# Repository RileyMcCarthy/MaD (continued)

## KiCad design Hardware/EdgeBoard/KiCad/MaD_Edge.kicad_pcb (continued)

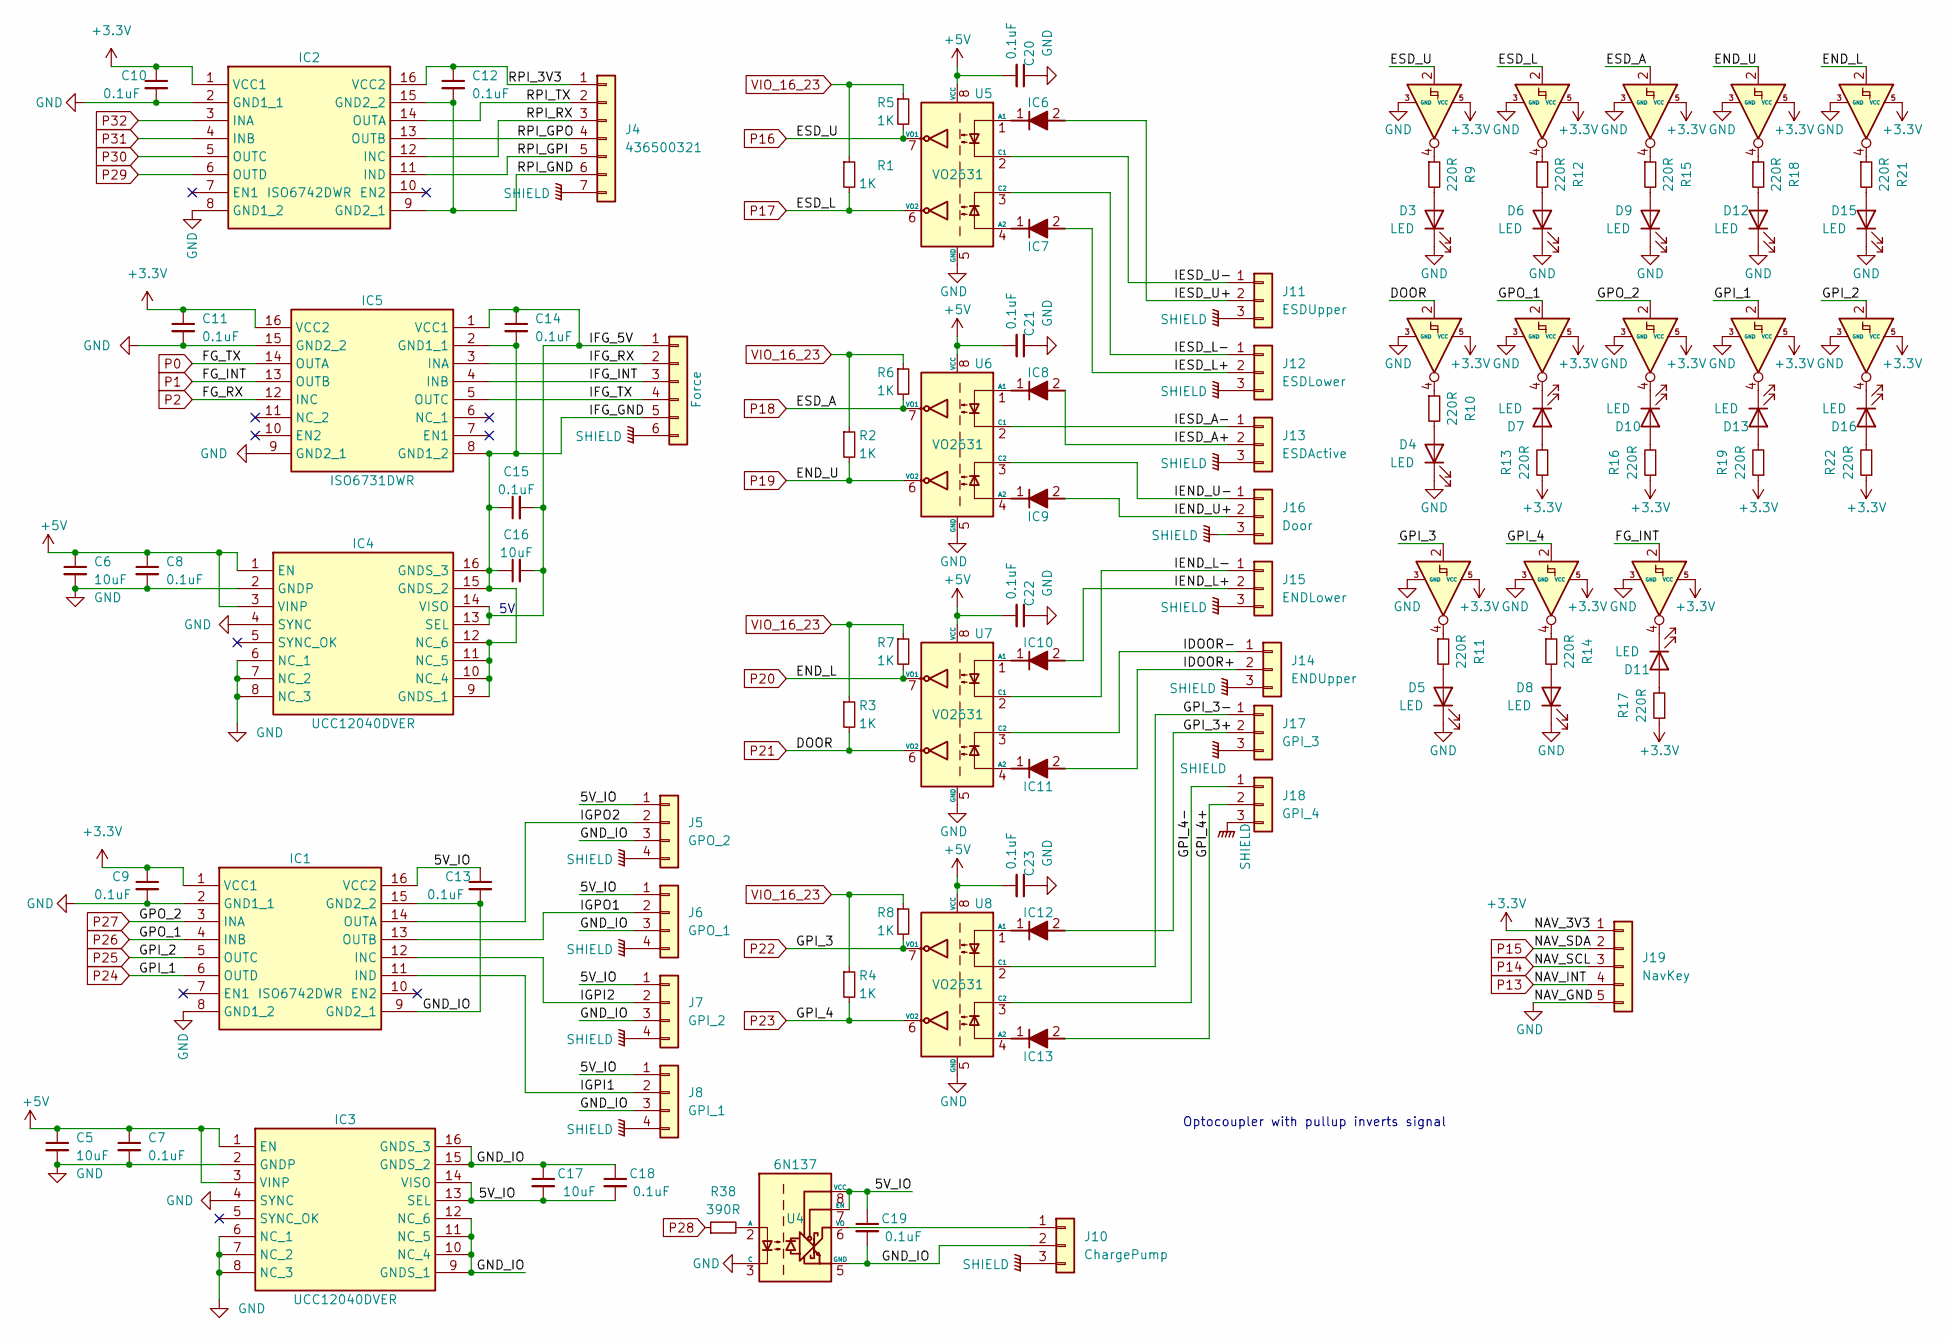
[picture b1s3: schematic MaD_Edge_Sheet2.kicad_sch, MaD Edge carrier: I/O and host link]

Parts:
C5, C6, C16, C17: 10uF; C_1206_3216Metric; Manufacturer_Part_Number CL31A106MAHNNNE; DIGIKEY 1276-1181-1-ND
C7, C8, C9, C10, C11, C12, C13, C14, C15, C18, C19, C20, C21, C22, C23: 0.1uF; C_0603_1608Metric; Manufacturer_Part_Number CL05A104KA5NNNC; DIGIKEY 1276-1043-1-ND
D3, D4, D5, D6, D7, D8, D9, D10, D11, D12, D13, D15, D16: LED; LED_0603_1608Metric; Manufacturer_Part_Number LTST-C190KGKT; DIGIKEY 160-1435-1-ND
IC1, IC2: ISO6742DWR; SOIC127P1030X265-16N; Manufacturer_Part_Number ISO6742DWR; DIGIKEY 296-ISO6742DWRCT-ND
IC3, IC4: UCC12040DVER; SOIC127P1030X265-16N; Manufacturer_Part_Number UCC12040DVER; DIGIKEY 296-UCC12040DVERCT-ND
IC5: ISO6731DWR; SOIC127P1030X265-16N; Manufacturer_Part_Number ISO6731DWR; DIGIKEY 296-ISO6731DWRCT-ND
IC6, IC7, IC8, IC9, IC10, IC11, IC12, IC13: NSI50010YT1G; SOD3716X135N; Manufacturer_Part_Number NSI50010YT1G; DIGIKEY NSI50010YT1G
J4: 436500321; Molex_Micro-Fit_3.0_43045-0618_2x03-1MP_P3.00mm_Vertical; Manufacturer_Part_Number 0430450618; DIGIKEY WM1803CT-ND
J5: GPO_2; Molex_Micro-Fit_3.0_43045-0415_2x02_P3.00mm_Vertical; Manufacturer_Part_Number 0430450415; DIGIKEY WM3251CT-ND
J6: GPO_1; Molex_Micro-Fit_3.0_43045-0415_2x02_P3.00mm_Vertical; Manufacturer_Part_Number 0430450415; DIGIKEY WM3251CT-ND
J7: GPI_2; Molex_Micro-Fit_3.0_43045-0415_2x02_P3.00mm_Vertical; Manufacturer_Part_Number 0430450415; DIGIKEY WM3251CT-ND
J8: GPI_1; Molex_Micro-Fit_3.0_43045-0415_2x02_P3.00mm_Vertical; Manufacturer_Part_Number 0430450415; DIGIKEY WM3251CT-ND
J9: Force; Molex_Micro-Fit_3.0_43045-0615_2x03_P3.00mm_Vertical; Manufacturer_Part_Number 0430450615; DIGIKEY WM6688CT-ND
J10: ChargePump; Molex_Micro-Fit_3.0_43650-0321_1x03_P3.00mm_Vertical; Manufacturer_Part_Number 0436500321; DIGIKEY WM14311CT-ND
J11: ESDUpper; Molex_Micro-Fit_3.0_43650-0321_1x03_P3.00mm_Vertical; Manufacturer_Part_Number 0436500321; DIGIKEY WM14311CT-ND
J12: ESDLower; Molex_Micro-Fit_3.0_43650-0321_1x03_P3.00mm_Vertical; Manufacturer_Part_Number 0436500321; DIGIKEY WM14311CT-ND
J13: ESDActive; Molex_Micro-Fit_3.0_43650-0321_1x03_P3.00mm_Vertical; Manufacturer_Part_Number 0436500321; DIGIKEY WM14311CT-ND
J14: ENDUpper; Molex_Micro-Fit_3.0_43650-0321_1x03_P3.00mm_Vertical; Manufacturer_Part_Number 0436500321; DIGIKEY WM14311CT-ND
J15: ENDLower; Molex_Micro-Fit_3.0_43650-0321_1x03_P3.00mm_Vertical; Manufacturer_Part_Number 0436500321; DIGIKEY WM14311CT-ND
J16: Door; Molex_Micro-Fit_3.0_43650-0321_1x03_P3.00mm_Vertical; Manufacturer_Part_Number 0436500321; DIGIKEY WM14311CT-ND
J17: GPI_3; Molex_Micro-Fit_3.0_43650-0321_1x03_P3.00mm_Vertical; Manufacturer_Part_Number 0436500321; DIGIKEY WM14311CT-ND
J18: GPI_4; Molex_Micro-Fit_3.0_43650-0321_1x03_P3.00mm_Vertical; Manufacturer_Part_Number 0436500321; DIGIKEY WM14311CT-ND
J19: NavKey; Molex_Micro-Fit_3.0_43650-0521_1x05_P3.00mm_Vertical; Manufacturer_Part_Number 0436500521; DIGIKEY WM14316CT-ND
R1, R2, R3, R4, R5, R6, R7, R8: 1K; R_0603_1608Metric; manufacturer_part_numbe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 0603WAF1001T5E; LCSC C21190
R9, R10, R11, R12, R13, R14, R15, R16, R17, R18, R19, R21, R22: 220R; R_0603_1608Metric; manufacturer_part_numbe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 0603WAF2200T5E; LCSC C22962
R38: 390R; R_0603_1608Metric; manufacturer_part_numbe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 0603WAF3900T5E; LCSC C23151
U4: 6N137; DIP-8_W7.62mm; Manufacturer_Part_Number 6N137; LCSC C2904408
U5, U6, U7, U8: VO2631; DIP-8_W7.62mm; Manufacturer_Part_Number VO2631; LCSC C511606
U9, U10, U11, U12, U13, U14, U15, U16, U17, U18, U19, U21, U22: SN74LVC1G14DBV; SOT-23-5; Manufacturer_Part_Number SN74LVC1G14DBVT; LCSC C5250998

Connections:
+3.3V: C9.1, C10.1, C11.1, IC1.1 (VCC1), IC2.1 (VCC1), IC5.16 (VCC2), J19.1, R13.1, R16.1, R17.1, R19.1, R22.1, U9.5 (VCC), U10.5 (VCC), U11.5 (VCC), U12.5 (VCC), U13.5 (VCC), U14.5 (VCC), U15.5 (VCC), U16.5 (VCC), U17.5 (VCC), U18.5 (VCC), U19.5 (VCC), U21.5 (VCC), U22.5 (VCC); also elsewhere on the board
+5V: C5.1, C6.1, C7.1, C8.1, C20.2, C21.2, C22.2, C23.2, IC3.1 (EN), IC3.3 (VINP), IC4.1 (EN), IC4.3 (VINP), U5.8 (VCC), U6.8 (VCC), U7.8 (VCC), U8.8 (VCC); also elsewhere on the board
/MaD_Edge_Sheet2/5V_IO: C13.1, C17.2, C18.2, C19.1, IC1.16 (VCC2), IC3.13 (SEL), IC3.14 (VISO), J5.1, J6.1, J7.1, J8.1, U4.7 (EN), U4.8 (VCC)
/MaD_Edge_Sheet2/GND_IO: C13.2, C17.1, C18.1, C19.2, IC1.9 (GND2_1), IC1.15 (GND2_2), IC3.9 (GNDS_1), IC3.10 (NC_4), IC3.11 (NC_5), IC3.12 (NC_6), IC3.15 (GNDS_2), IC3.16 (GNDS_3), J5.3, J6.3, J7.3, J8.3, J10.2, U4.5 (GND)
/MaD_Edge_Sheet2/GPI_3+: IC12.2 (A), J17.2
/MaD_Edge_Sheet2/GPI_3-: J17.1, U8.2 (C1)
/MaD_Edge_Sheet2/GPI_4+: IC13.2 (A), J18.2
/MaD_Edge_Sheet2/GPI_4-: J18.1, U8.3 (C2)
/MaD_Edge_Sheet2/IDOOR+: IC11.2 (A), J14.2
/MaD_Edge_Sheet2/IDOOR-: J14.1, U7.3 (C2)
/MaD_Edge_Sheet2/IEND_L+: IC10.2 (A), J15.2
/MaD_Edge_Sheet2/IEND_L-: J15.1, U7.2 (C1)
/MaD_Edge_Sheet2/IEND_U+: IC9.2 (A), J16.2
/MaD_Edge_Sheet2/IEND_U-: J16.1, U6.3 (C2)
/MaD_Edge_Sheet2/IESD_A+: IC8.2 (A), J13.2
/MaD_Edge_Sheet2/IESD_A-: J13.1, U6.2 (C1)
/MaD_Edge_Sheet2/IESD_L+: IC7.2 (A), J12.2
/MaD_Edge_Sheet2/IESD_L-: J12.1, U5.3 (C2)
/MaD_Edge_Sheet2/IESD_U+: IC6.2 (A), J11.2
/MaD_Edge_Sheet2/IESD_U-: J11.1, U5.2 (C1)
/MaD_Edge_Sheet2/IFG_5V: C14.1, C15.2, C16.2, IC4.13 (SEL), IC4.14 (VISO), IC5.1 (VCC1), J9.1
/MaD_Edge_Sheet2/IFG_GND: C14.2, C15.1, C16.1, IC4.9 (GNDS_1), IC4.10 (NC_4), IC4.11 (NC_5), IC4.12 (NC_6), IC4.15 (GNDS_2), IC4.16 (GNDS_3), IC5.2 (GND1_1), IC5.8 (GND1_2), J9.5
/MaD_Edge_Sheet2/IFG_INT: IC5.4 (INB), J9.3
/MaD_Edge_Sheet2/IFG_RX: IC5.3 (INA), J9.2
/MaD_Edge_Sheet2/IFG_TX: IC5.5 (OUTC), J9.4
/MaD_Edge_Sheet2/IGPI1: IC1.11 (IND), J8.2
/MaD_Edge_Sheet2/IGPI2: IC1.12 (INC), J7.2
/MaD_Edge_Sheet2/IGPO1: IC1.13 (OUTB), J6.2
/MaD_Edge_Sheet2/IGPO2: IC1.14 (OUTA), J5.2
/MaD_Edge_Sheet2/RPI_3V3: C12.1, IC2.16 (VCC2), J4.1
/MaD_Edge_Sheet2/RPI_GND: C12.2, IC2.9 (GND2_1), IC2.15 (GND2_2), J4.6
/MaD_Edge_Sheet2/RPI_GPI: IC2.11 (IND), J4.5
/MaD_Edge_Sheet2/RPI_GPO: IC2.13 (OUTB), J4.4
/MaD_Edge_Sheet2/RPI_RX: IC2.12 (INC), J4.3
/MaD_Edge_Sheet2/RPI_TX: IC2.14 (OUTA), J4.2
GND: C5.2, C6.2, C7.2, C8.2, C9.2, C10.2, C11.2, C20.1, C21.1, C22.1, C23.1, D3.1 (K), D4.1 (K), D5.1 (K), D6.1 (K), D8.1 (K), D9.1 (K), D12.1 (K), D15.1 (K), IC1.2 (GND1_1), IC1.8 (GND1_2), IC2.2 (GND1_1), IC2.8 (GND1_2), IC3.2 (GNDP), IC3.4 (SYNC), IC3.6 (NC_1), IC3.7 (NC_2), IC3.8 (NC_3), IC4.2 (GNDP), IC4.4 (SYNC), IC4.6 (NC_1), IC4.7 (NC_2), IC4.8 (NC_3), IC5.9 (GND2_1), IC5.15 (GND2_2), J19.5, U4.3 (C), U5.5 (GND), U6.5 (GND), U7.5 (GND), U8.5 (GND), U9.3 (GND), U10.3 (GND), U11.3 (GND), U12.3 (GND), U13.3 (GND), U14.3 (GND), U15.3 (GND), U16.3 (GND), U17.3 (GND), U18.3 (GND), U19.3 (GND), U21.3 (GND), U22.3 (GND); also elsewhere on the board
unnamed: D3.2 (A), R9.2
unnamed: D4.2 (A), R10.2
unnamed: D5.2 (A), R11.2
unnamed: D6.2 (A), R12.2
unnamed: D7.2 (A), R13.2
unnamed: D7.1 (K), U13.4
unnamed: D8.2 (A), R14.2
unnamed: D9.2 (A), R15.2
unnamed: D10.2 (A), R16.2
unnamed: D10.1 (K), U16.4
unnamed: D11.2 (A), R17.2
unnamed: D11.1 (K), U17.4
unnamed: D12.2 (A), R18.2
unnamed: D13.2 (A), R19.2
unnamed: D13.1 (K), U19.4
unnamed: D15.2 (A), R21.2
unnamed: D16.2 (A), R22.2
unnamed: D16.1 (K), U22.4
unnamed: IC6.1 (K), U5.1 (A1)
unnamed: IC7.1 (K), U5.4 (A2)
unnamed: IC8.1 (K), U6.1 (A1)
unnamed: IC9.1 (K), U6.4 (A2)
unnamed: IC10.1 (K), U7.1 (A1)
unnamed: IC11.1 (K), U7.4 (A2)
unnamed: IC12.1 (K), U8.1 (A1)
unnamed: IC13.1 (K), U8.4 (A2)
unnamed: J10.1, U4.6 (VO)
unnamed: R9.1, U9.4
unnamed: R10.1, U10.4
unnamed: R11.1, U11.4
unnamed: R12.1, U12.4
unnamed: R14.1, U14.4
unnamed: R15.1, U15.4
unnamed: R18.1, U18.4
unnamed: R21.1, U21.4
unnamed: R38.2, U4.2 (A)
P0: IC5.14 (OUTA); also elsewhere on the board
P1: IC5.13 (OUTB), U17.2; also elsewhere on the board
P2: IC5.12 (INC); also elsewhere on the board
P13: J19.4; also elsewhere on the board
P14: J19.3; also elsewhere on the board
P15: J19.2; also elsewhere on the board
P16: R5.2, U5.7 (VO1), U9.2; also elsewhere on the board
P17: R1.2, U5.6 (VO2), U12.2; also elsewhere on the board
P18: R6.2, U6.7 (VO1), U15.2; also elsewhere on the board
P19: R2.2, U6.6 (VO2), U18.2; also elsewhere on the board
P20: R7.2, U7.7 (VO1), U21.2; also elsewhere on the board
P21: R3.2, U7.6 (VO2), U10.2; also elsewhere on the board
P22: R8.2, U8.7 (VO1), U11.2; also elsewhere on the board
P23: R4.2, U8.6 (VO2), U14.2; also elsewhere on the board
P24: IC1.6 (OUTD), U19.2; also elsewhere on the board
P25: IC1.5 (OUTC), U22.2; also elsewhere on the board
P26: IC1.4 (INB), U13.2; also elsewhere on the board
P27: IC1.3 (INA), U16.2; also elsewhere on the board
P28: R38.1; also elsewhere on the board
P29: IC2.6 (OUTD); also elsewhere on the board
P30: IC2.5 (OUTC); also elsewhere on the board
P31: IC2.4 (INB); also elsewhere on the board
P32: IC2.3 (INA); also elsewhere on the board
SHIELD: J4.7, J5.4, J6.4, J7.4, J8.4, J9.6, J10.3, J11.3, J12.3, J13.3, J14.3, J15.3, J16.3, J17.3, J18.3; also elsewhere on the board
VIO_16_23: R1.1, R2.1, R3.1, R4.1, R5.1, R6.1, R7.1, R8.1; also elsewhere on the board

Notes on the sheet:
Optocoupler with pullup inverts signal

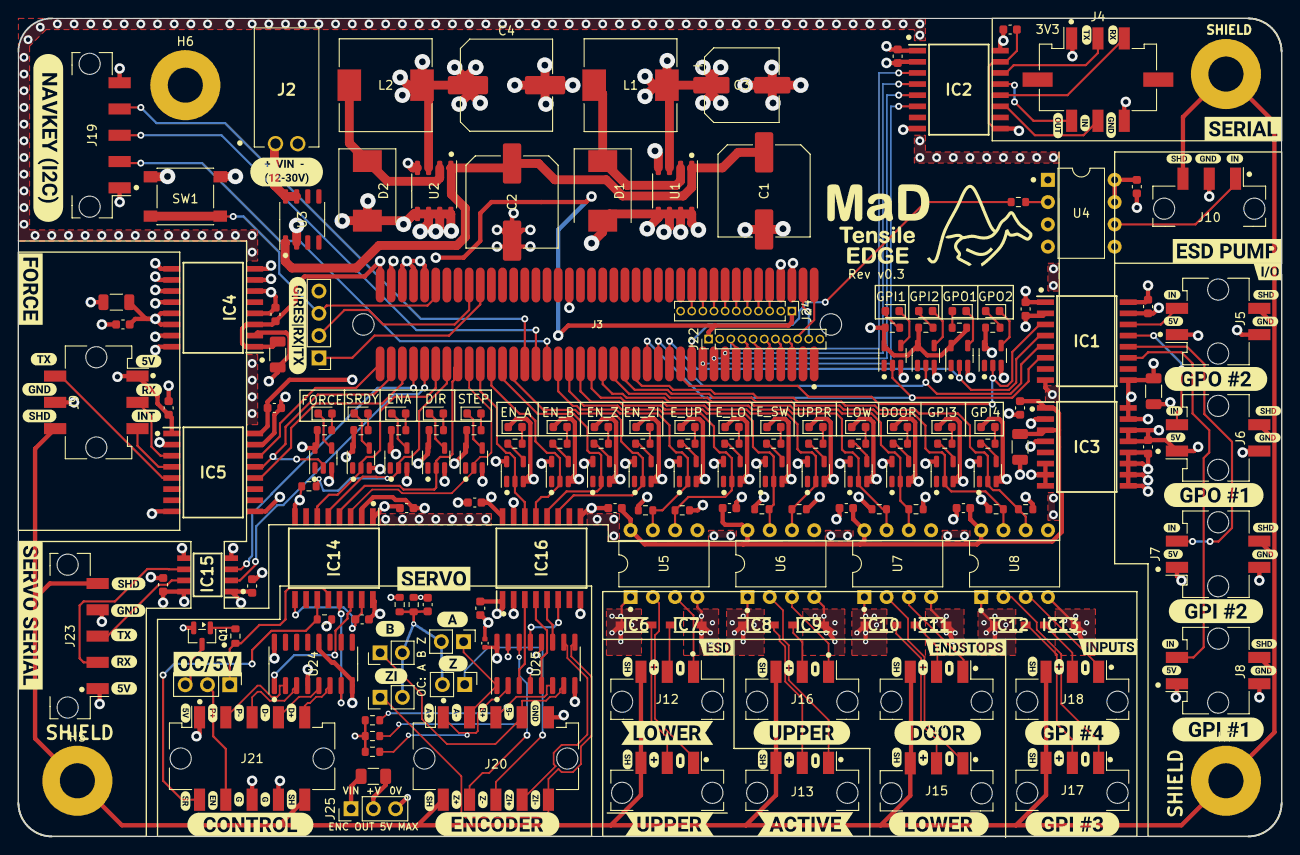
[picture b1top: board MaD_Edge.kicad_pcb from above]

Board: 4 copper layers, 144.1 x 93.3 mm, 288 parts (0 on the bottom side), 179 nets.

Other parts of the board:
kibuzzard-6474CD2A: G***; kibuzzard-6474CD2A
kibuzzard-6474CD43: G***; kibuzzard-6474CD43
kibuzzard-6474CE56: G***; kibuzzard-6474CE56
kibuzzard-6474CEBE: G***; kibuzzard-6474CEBE
kibuzzard-6474CEDF: G***; kibuzzard-6474CEDF
kibuzzard-6474CEEB: G***; kibuzzard-6474CEEB
kibuzzard-6474CF4E: G***; kibuzzard-6474CF4E
kibuzzard-6474CF37: G***; kibuzzard-6474CF37
kibuzzard-6474D1C6: G***; kibuzzard-6474D1C6
kibuzzard-6474D2B0: G***; kibuzzard-6474D2B0
kibuzzard-6474D2C7: G***; kibuzzard-6474D2C7
kibuzzard-6474D2DE: G***; kibuzzard-6474D2DE
kibuzzard-6474D3A4: G***; kibuzzard-6474D3A4
kibuzzard-6474D3B5: G***; kibuzzard-6474D3B5
kibuzzard-6474D3C7: G***; kibuzzard-6474D3C7
kibuzzard-6474D3D9: G***; kibuzzard-6474D3D9
kibuzzard-6474D10F: G***; kibuzzard-6474D10F
kibuzzard-6474D11D: G***; kibuzzard-6474D11D
kibuzzard-6474D12A: G***; kibuzzard-6474D12A
kibuzzard-6474D26F: G***; kibuzzard-6474D26F
kibuzzard-6474D36B: G***; kibuzzard-6474D36B
kibuzzard-6474D37E: G***; kibuzzard-6474D37E
kibuzzard-6474D215: G***; kibuzzard-6474D215
kibuzzard-6474D298: G***; kibuzzard-6474D298
kibuzzard-64776FD8: G***; kibuzzard-64776FD8
kibuzzard-647770C7, kibuzzard-647770C7#2: G***; kibuzzard-647770C7
kibuzzard-647770D0: G***; kibuzzard-647770D0
kibuzzard-647770D6: G***; kibuzzard-647770D6
kibuzzard-647771C1: G***; kibuzzard-647771C1
kibuzzard-647772E1: G***; kibuzzard-647772E1
kibuzzard-647772FA: G***; kibuzzard-647772FA
kibuzzard-647774DE: G***; kibuzzard-647774DE
kibuzzard-647775A2: G***; kibuzzard-647775A2
kibuzzard-647777A9, kibuzzard-647777A9#2, kibuzzard-647777A9#3, kibuzzard-647777A9#4: G***; kibuzzard-647777A9
kibuzzard-647777B2, kibuzzard-647777B2#2, kibuzzard-647777B2#3, kibuzzard-647777B2#4: G***; kibuzzard-647777B2
kibuzzard-647778CC: G***; kibuzzard-647778CC
kibuzzard-647778DF: G***; kibuzzard-647778DF
kibuzzard-647778EA: G***; kibuzzard-647778EA
kibuzzard-6477707F: G***; kibuzzard-6477707F
kibuzzard-6477708A: G***; kibuzzard-6477708A
kibuzzard-6477713B: G***; kibuzzard-6477713B
kibuzzard-6477715F: G***; kibuzzard-6477715F
kibuzzard-6477723E: G***; kibuzzard-6477723E
kibuzzard-6477742A: G***; kibuzzard-6477742A
kibuzzard-6477743C: G***; kibuzzard-6477743C
kibuzzard-6477745C: G***; kibuzzard-6477745C
kibuzzard-6477746F: G***; kibuzzard-6477746F
kibuzzard-6477757D: G***; kibuzzard-6477757D
kibuzzard-6477779F, kibuzzard-6477779F#2, kibuzzard-6477779F#3, kibuzzard-6477779F#4: G***; kibuzzard-6477779F
kibuzzard-64777084: G***; kibuzzard-64777084
kibuzzard-64777131: G***; kibuzzard-64777131
kibuzzard-64777136: G***; kibuzzard-64777136
kibuzzard-64777256: G***; kibuzzard-64777256
kibuzzard-64777263: G***; kibuzzard-64777263
kibuzzard-64777279: G***; kibuzzard-64777279
kibuzzard-64777285: G***; kibuzzard-64777285
kibuzzard-64777339, kibuzzard-64777339#2: G***; kibuzzard-64777339
kibuzzard-64777365, kibuzzard-64777365#2: G***; kibuzzard-64777365
kibuzzard-64777421: G***; kibuzzard-64777421
kibuzzard-64777448: G***; kibuzzard-64777448
kibuzzard-64777463: G***; kibuzzard-64777463
kibuzzard-64777469: G***; kibuzzard-64777469
kibuzzard-64777566: G***; kibuzzard-64777566
kibuzzard-64777573: G***; kibuzzard-64777573
kibuzzard-64777588: G***; kibuzzard-64777588
kibuzzard-64777629, kibuzzard-64777629#2, kibuzzard-64777629#3, kibuzzard-64777629#4, kibuzzard-64777629#5, kibuzzard-64777629#6, kibuzzard-64777629#7, kibuzzard-64777629#8: G***; kibuzzard-64777629
kibuzzard-64777654, kibuzzard-64777654#2, kibuzzard-64777654#3, kibuzzard-64777654#4, kibuzzard-64777654#5, kibuzzard-64777654#6, kibuzzard-64777654#7, kibuzzard-64777654#8: G***; kibuzzard-64777654
kibuzzard-64777688, kibuzzard-64777688#2, kibuzzard-64777688#3, kibuzzard-64777688#4, kibuzzard-64777688#5, kibuzzard-64777688#6, kibuzzard-64777688#7, kibuzzard-64777688#8: G***; kibuzzard-64777688
kibuzzard-64777781, kibuzzard-64777781#2, kibuzzard-64777781#3, kibuzzard-64777781#4: G***; kibuzzard-64777781
kibuzzard-64777814: G***; kibuzzard-64777814
kibuzzard-64777822: G***; kibuzzard-64777822
kibuzzard-64777848: G***; kibuzzard-64777848
kibuzzard-64777917: G***; kibuzzard-64777917
kibuzzard-64777922: G***; kibuzzard-64777922

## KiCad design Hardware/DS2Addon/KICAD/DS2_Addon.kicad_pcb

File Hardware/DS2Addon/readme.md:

# DS2 Addon

The **DS2 Addon** is a piggyback board for the **DS2 force gauge**. It conditions
the strain-gauge signal and presents an analog voltage that the firmware reads
through the **ADS122U04** ADC, giving the machine its force measurement.

## Role in the machine

- Interfaces the DS2 force gauge's strain-gauge bridge to the
  [EdgeBoard](../EdgeBoard/readme.md).
- Feeds the analog force signal to the ADS122U04 ADC (driven by `IO_ADS122U04`
  in the [firmware](../../Firmware/MaDCore)).
- Provides the force-path measurement used for live readouts, limit enforcement,
  and stress calculation.

## Bench testing

Notes for exercising the board on the bench (no gauge, talking straight to a
P2-EVAL), learned during hardware bring-up:

- **Power the analog domain.** The analog supply is fully isolated from the
  digital 3V3: **AVDD/AGND normally come from the DS2 gauge via J2**, so a bare
  board has the ADC's analog side unpowered. For bench tests strap
  **J2.1 (AVDD) → 3.3 V** and **J2.2 (AGND) → GND**. **Remove the straps before
  connecting the real gauge** — its supply must not fight the bench rail.
- **Close the input jumpers.** The A0/A1 signal path is open by default:
  **R6/R7 are DNP**, so close solder jumpers **JP1/JP2** to route the analog
  inputs through to the ADC.
- **Serial wiring.** The firmware (`IO_ADS122U04`) expects the piggy silk
  **"RX" wired to EVAL P2** and silk **"TX" to EVAL P0**, running at
  **115200 baud**.
- **~RESET pull-up (pre-R10 boards).** Boards fabricated before the **R10**
  10 kΩ pull-up was added float the ADS122U04's ~RESET pin, and the chip will
  not respond to any UART command. On those boards tie ~RESET to 3.3 V manually
  (e.g. bridge U1 pins 1-2-3 and feed 3.3 V via the J3 GPIO0 hole).

## Working with the design

This is a [KiCad](https://www.kicad.org/) project (under `KICAD/`). Open the
`.kicad_pro` to view or edit it. Manufacturing files are produced by the hardware
CI job and published on `hardware-v*` tags — see the
[CI/CD docs](https://rileymccarthy.github.io/MaD/dev/ci-cd-and-releases/).

### Rev 2 (pcbc)

`pcbc/ds2_addon.py` is an in-progress rev 2 of this board, described in Python
and compiled to KiCad files by the pcbc tool (KiCad 10 format, under
`pcbc/layout/`). It has not been fabricated and CI does not build it. `KICAD/`
remains the fabricated rev 1 and the source for CI and releases.

## Documentation

See the
[Hardware overview](https://rileymccarthy.github.io/MaD/how-it-works/hardware/)
for how the force path works end-to-end.

> **Status:** schematic notes and a bill of materials are still being written.

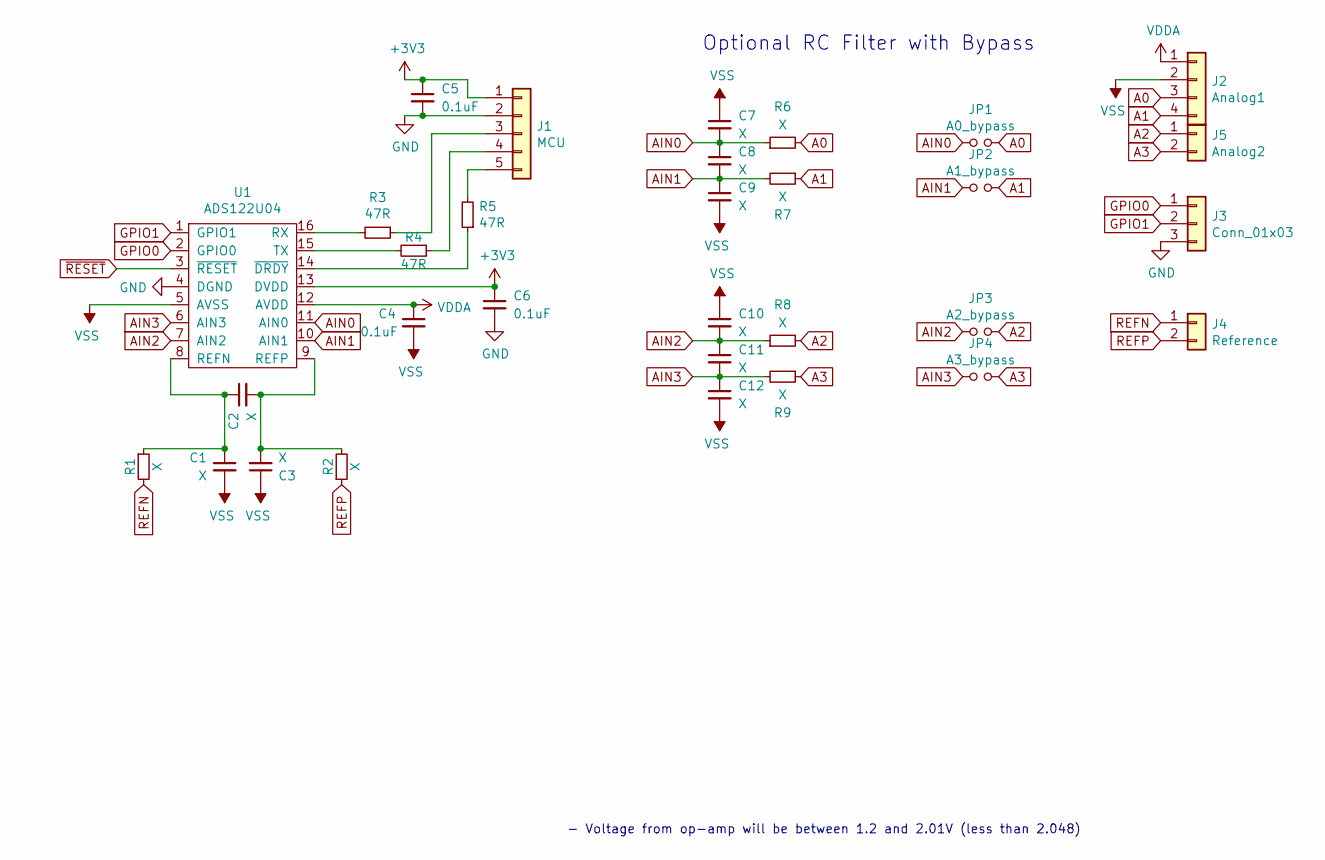
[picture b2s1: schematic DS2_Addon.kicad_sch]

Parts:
C1, C2, C3, C7, C8, C9, C10, C11, C12: X; C_0805_2012Metric
C4, C5, C6: 0.1uF; C_0805_2012Metric; LCSC C49678
J1: MCU; PinHeader_1x05_P2.54mm_Vertical
J2: Analog1; PinHeader_1x04_P2.54mm_Vertical
J3: Conn_01x03; PinHeader_1x03_P2.54mm_Vertical
J4: Reference; PinHeader_1x02_P2.54mm_Vertical
J5: Analog2; PinHeader_1x02_P2.54mm_Vertical
JP1: A0_bypass; SolderJumper-2_P1.3mm_Open_Pad1.0x1.5mm
JP2: A1_bypass; SolderJumper-2_P1.3mm_Open_Pad1.0x1.5mm
JP3: A2_bypass; SolderJumper-2_P1.3mm_Open_Pad1.0x1.5mm
JP4: A3_bypass; SolderJumper-2_P1.3mm_Open_Pad1.0x1.5mm
R1, R2, R6, R7, R8, R9: X; R_0805_2012Metric
R3, R4, R5: 47R; R_0805_2012Metric; LCSC C17714
U1: ADS122U04; TSSOP-16_4.4x5mm_P0.65mm

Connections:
+3V3: C5.1, C6.1, J1.1, U1.13 (DVDD); also elsewhere on the board
A0: J2.3, JP1.2, R6.2
A1: J2.4, JP2.2, R7.1
A2: J5.1, JP3.2, R8.2
A3: J5.2, JP4.2, R9.1
AIN0: C7.2, C8.1, JP1.1, R6.1, U1.11 (AIN0)
AIN1: C8.2, C9.1, JP2.1, R7.2, U1.10 (AIN1)
AIN2: C10.2, C11.1, JP3.1, R8.1, U1.7 (AIN2)
AIN3: C11.2, C12.1, JP4.1, R9.2, U1.6 (AIN3)
GND: C5.2, C6.2, J1.2, J3.3, U1.4 (DGND)
GPIO0: J3.1, U1.2 (GPIO0)
GPIO1: J3.2, U1.1 (GPIO1)
unnamed: C1.1, C2.1, R1.1, U1.8 (REFN)
unnamed: C2.2, C3.2, R2.2, U1.9 (REFP)
unnamed: J1.3, R3.1
unnamed: J1.4, R4.1
unnamed: J1.5, R5.2
unnamed: R3.2, U1.16 (RX)
unnamed: R4.2, U1.15 (TX)
unnamed: R5.1, U1.14 (~DRDY)
REFN: J4.1, R1.2
REFP: J4.2, R2.1
VDDA: C4.1, J2.1, U1.12 (AVDD)
VSS: C1.2, C3.1, C4.2, C7.1, C9.2, C10.1, C12.2, J2.2, U1.5 (AVSS)
~RESET: U1.3 (~RESET); also elsewhere on the board

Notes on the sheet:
Optional RC Filter with Bypass
- Voltage from op-amp will be between 1.2 and 2.01V (less than 2.048)

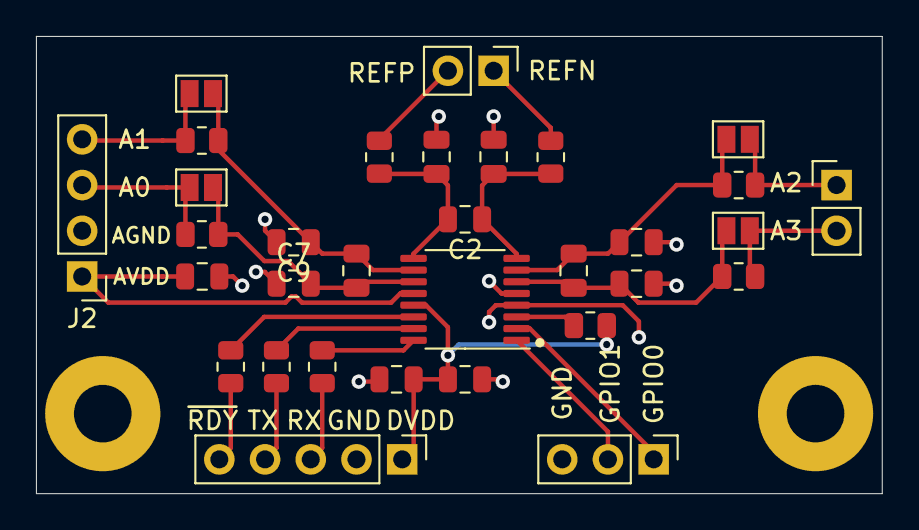
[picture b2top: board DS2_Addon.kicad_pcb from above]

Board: 2 copper layers, 47.0 x 25.4 mm, 33 parts (1 on the bottom side), 25 nets.

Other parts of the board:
LOGO: LOGO
R10: 10k; R_0805_2012Metric

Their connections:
+3V3: R10.2; also elsewhere on the board
~RESET: R10.1; also elsewhere on the board

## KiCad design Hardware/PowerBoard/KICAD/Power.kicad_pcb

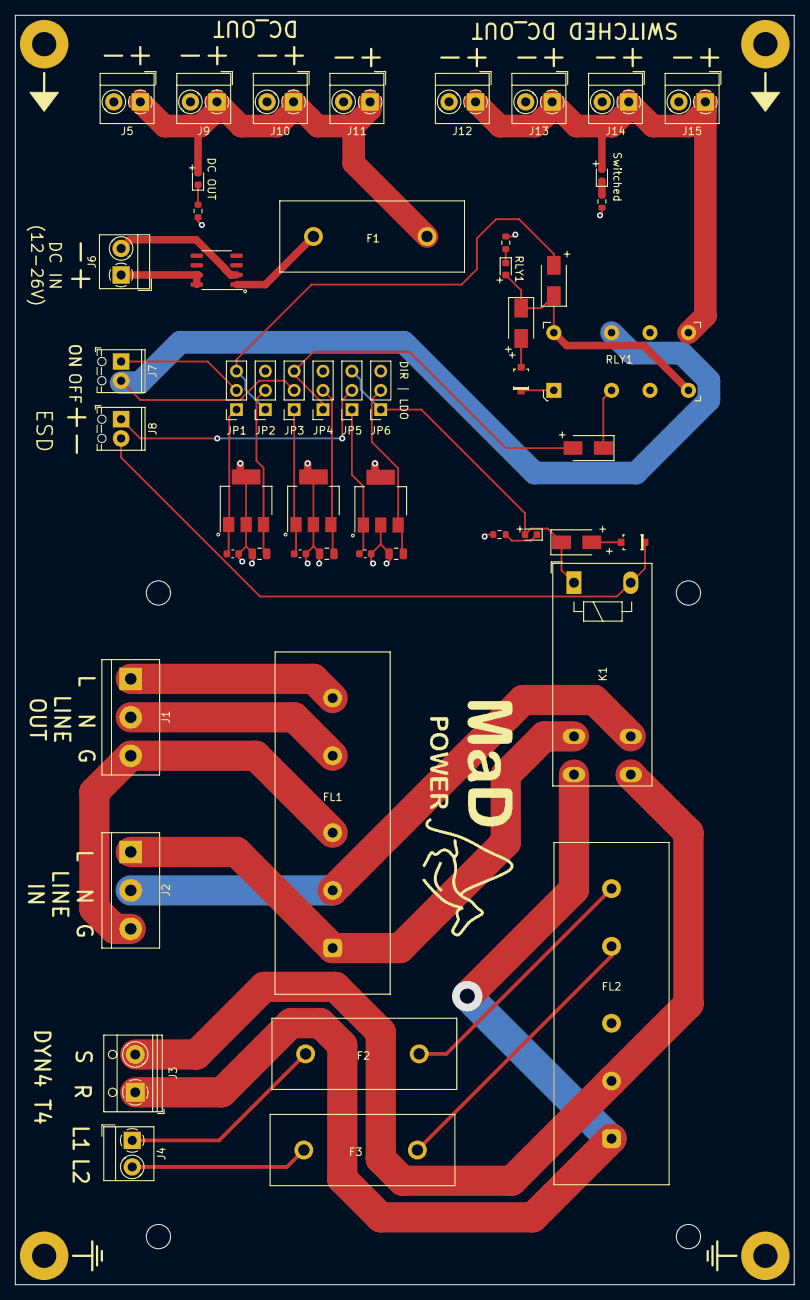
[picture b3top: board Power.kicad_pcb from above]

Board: 2 copper layers, 102.9 x 167.6 mm, 57 parts (0 on the bottom side), 37 nets.

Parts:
C1, C2, C3: 0.47uF; C_0603_1608Metric
C4, C5, C6: 22uF; C_0805_2012Metric
D1: GRN; LED_0603_1608Metric
D2: RED; LED_0603_1608Metric
D3, D4, D5, D6: SS14 DO-214 AC (40V 1A); D_SMA
D7, D8: BLU; LED_0603_1608Metric
F1: Wurth 696106003002‎; 732-11374-ND
F2, F3: Wurth 696106003002‎ (15mm x 1.5mm); 732-11374-ND
FL1, FL2: FN406-1-02; Filter_Schaffner_FN406
H1, H2, H3, H4: MountingHole_Pad; MountingHole_3.2mm_M3_Pad
J1, J2: 5.08mmx1mm; TerminalBlock_bornier-3_P5.08mm
J3: 5mmx1mm; TerminalBlock_RND_205-00012_1x02_P5.00mm_Horizontal
J4, J6: 3.5mmx1mm; TerminalBlock_MetzConnect_Type059_RT06302HBWC_1x02_P3.50mm_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
J5, J9, J10, J11, J12, J13, J14, J15: 3.5mmx0.7mm; TerminalBlock_MetzConnect_Type059_RT06302HBWC_1x02_P3.50mm_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
J7, J8: 2.54mmx1mm; TerminalBlock_Phoenix_MPT-0,5-2-2.54_1x02_P2.54mm_Horizontal
JP1, JP2, JP3, JP4, JP5, JP6: Jumper_Ganged; PinSocket_1x03_P2.54mm_Vertical
K1: Schrack RTE44012; Relay_DPST_Schrack-RT2-FormA_RM5mm
LOGO: LOGO
R1, R2, R3, R4: 1k; R_0603_1608Metric
RLY1: Axicom V23105A5003A201; Relay_THT_G5V-2
U2: APM4953; SOP-8_3.9x4.9mm_P1.27mm
U3, U4, U5: LM2940G-12V-AA3-R; SOT-223-3_TabPin2
Z1, Z2: MM1Z15 SOD-123; SOD-123

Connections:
Coil_AC: D5.1, D8.2, JP5.3, JP6.1, K1.A1
Coil_DC: D6.2, JP1.3, JP2.1
DC_IN_+: D1.2, F1.2, J5.1, J9.1, J10.1, J11.1
DC_SW_+: D2.2, J12.1, J13.1, J14.1, J15.1, RLY1.9
ESD_+: J8.1, JP5.2
ESD_-: J8.2, K1.A2, Z2.K
Earth_Protective: FL1.3, FL2.3, H3.1, H4.1, J1.3, J2.3
GND: C1.2, C2.2, C3.2, C4.2, C5.2, C6.2, H1.1, H2.1, J5.2, J6.2, J9.2, J10.2, J11.2, J12.2, J13.2, J14.2, J15.2, R1.2, R2.2, R3.2, R4.2, RLY1.1, U2.2, U3.2, U4.2, U5.2, Z1.K
LDO_AC_IN: C3.1, JP5.1, U5.1
LDO_AC_OUT: C6.1, JP6.2, U5.3
LDO_OFF_IN: C2.1, JP3.1, U4.1
LDO_OFF_OUT: C5.1, JP4.2, U4.3
LDO_ON_IN: C1.1, JP1.1, U3.1
LDO_ON_OUT: C4.1, JP2.2, U3.3
LIne_Fuse: F2.2, FL2.5
LIne_Logic: F2.1, J4.1
Latch_DC: D3.2, JP3.3, JP4.1
Line_DC_PWR: FL1.5, J1.1
Line_IN: FL1.1, J2.1, K1.11
Line_Servo: FL2.1, J3.1, K1.14
unnamed: D1.1, R1.1
unnamed: D2.1, R2.1
unnamed: D3.1, RLY1.4
unnamed: D4.1, D6.1, D7.2, RLY1.8, RLY1.16
unnamed: D4.2, Z1.A
unnamed: D5.2, Z2.A
unnamed: D7.1, R3.1
unnamed: D8.1, R4.1
unnamed: F1.1, U2.1
unnamed: J6.1, U2.7, U2.8
Neut_DC_PWR: FL1.4, J1.2
Neut_Fuse: F3.2, FL2.4
Neut_IN: FL1.2, J2.2, K1.21
Neut_Logic: F3.1, J4.2
Neut_Servo: FL2.2, J3.2, K1.24
SW_OFF: J7.2, JP3.2, RLY1.13
SW_ON: J7.1, JP1.2

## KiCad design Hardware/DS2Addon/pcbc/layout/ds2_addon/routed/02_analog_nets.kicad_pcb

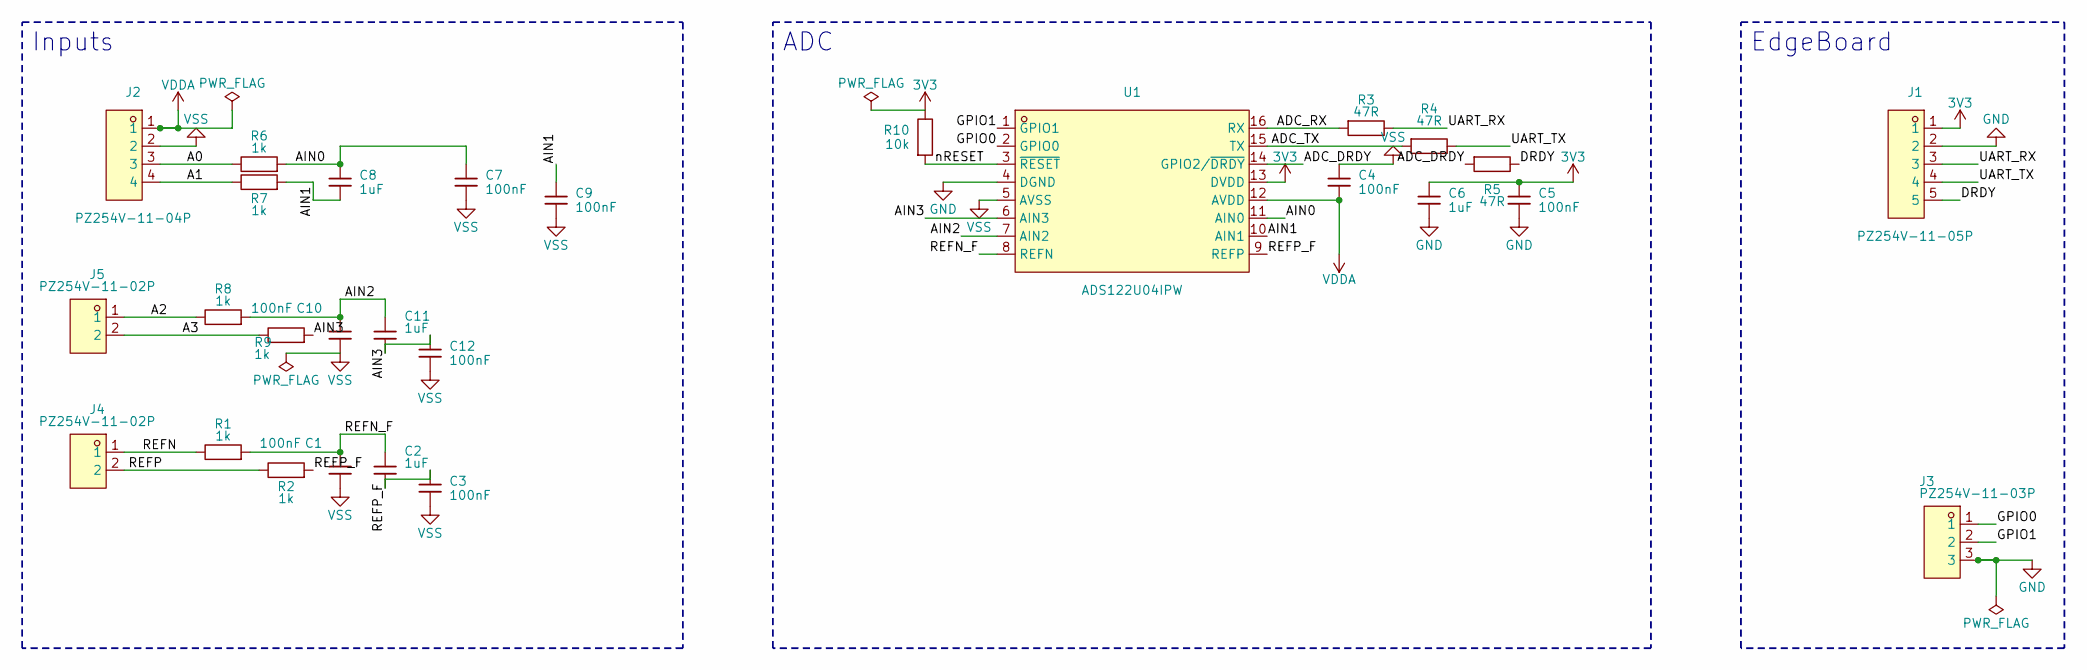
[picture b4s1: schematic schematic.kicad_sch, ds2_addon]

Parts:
C1, C3, C4, C5, C7, C9, C10, C12: 100nF
C2, C6, C8, C11: 1uF
J1: PZ254V-11-05P
J2: PZ254V-11-04P
J3: PZ254V-11-03P
J4, J5: PZ254V-11-02P
R1, R2, R6, R7, R8, R9: 1k
R3, R4, R5: 47R
R10: 10k
U1: ADS122U04IPW

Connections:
3V3: C5.1, C6.1, J1.1, R10.1, U1.13 (DVDD)
A0: J2.3, R6.1
A1: J2.4, R7.1
A2: J5.1, R8.1
A3: J5.2, R9.1
ADC_DRDY: R5.2, U1.14 (GPIO2/~DRDY)
ADC_RX: R3.2, U1.16 (RX)
ADC_TX: R4.2, U1.15 (TX)
AIN0: C7.1, C8.1, R6.2, U1.11 (AIN0)
AIN1: C8.2, C9.1, R7.2, U1.10 (AIN1)
AIN2: C10.1, C11.1, R8.2, U1.7 (AIN2)
AIN3: C11.2, C12.1, R9.2, U1.6 (AIN3)
DRDY: J1.5, R5.1
GND: C5.2, C6.2, J1.2, J3.3, U1.4 (DGND)
GPIO0: J3.1, U1.2 (GPIO0)
GPIO1: J3.2, U1.1 (GPIO1)
REFN: J4.1, R1.1
REFN_F: C1.1, C2.1, R1.2, U1.8 (REFN)
REFP: J4.2, R2.1
REFP_F: C2.2, C3.1, R2.2, U1.9 (REFP)
UART_RX: J1.3, R3.1
UART_TX: J1.4, R4.1
VDDA: C4.1, J2.1, U1.12 (AVDD)
VSS: C1.2, C3.2, C4.2, C7.2, C9.2, C10.2, C12.2, J2.2, U1.5 (AVSS)
nRESET: R10.2, U1.3 (~RESET)

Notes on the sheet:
Inputs
ADC
EdgeBoard

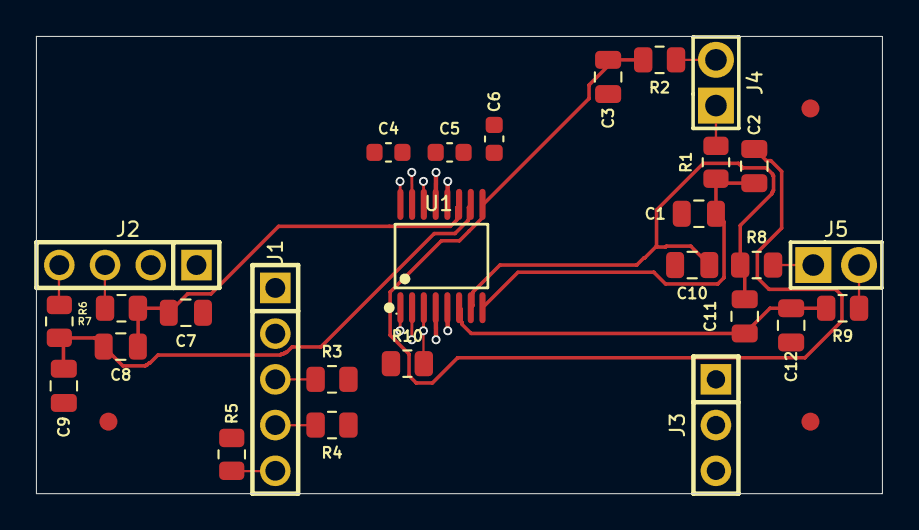
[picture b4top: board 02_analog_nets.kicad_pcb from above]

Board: 2 copper layers, 47.0 x 25.4 mm, 31 parts (0 on the bottom side), 25 nets.

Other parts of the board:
FID1, FID2, FID3: Fiducial_1mm_Mask2mm
